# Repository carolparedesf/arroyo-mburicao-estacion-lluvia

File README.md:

# Sistema de adquisición y visualización de datos de sensores de lluvia
### Estaciones meteorológicas distribuidas — Arroyo Mburicao

---

## Descripción

Sistema de monitoreo pluviométrico distribuido a lo largo del arroyo Mburicao. Cada estación integra un sensor óptico de lluvia con comunicación RS485, una PCB propia basada en ESP32-S3 con componentes SMD, y transmisión de datos vía DTU con respaldo local en MicroSD. Los datos se visualizan en tiempo real a través de un dashboard web.

---

## Imágenes del hardware

| Render 3D | PCB | Placa soldada |
|---|---|---|
|  |  |  |

## Características principales

- Microcontrolador ESP32-S3 con componentes de montaje superficial (SMD)
- Sensor óptico de lluvia con interfaz RS485 / Modbus RTU
- Transmisión de datos vía DTU (RS485 canal 2)
- Almacenamiento local en MicroSD (`datalog.csv`) con cola de reintentos (`temp.csv`)
- RTC DS3231M para sincronización de slots de medición cada 60 segundos
- Alimentación con reductor a 3.3V
- Caja para intemperie compatible con la estructura de la estación meteorológica
- Dashboard web en tiempo real

---

## Estructura del repositorio

```
arroyo-mburicao-estacion-lluvia/
│
├── hardware/
│   └── Estacion_lluviaV4/
│       ├── BOM/                           # Lista de materiales
│       ├── images/                        # Renders 3D y fotos del PCB
│       ├── planos/                        # Planos técnicos 2D con cotas
│       ├── step/                          # Modelos 3D STEP
│       ├── Estacion_lluviaV4.kicad_pcb    # PCB
│       ├── Estacion_lluviaV4.kicad_sch    # Esquemático principal
│       ├── conector_USB.kicad_sch         # Sub-esquemático USB
│       ├── DS3231.kicad_sch               # Sub-esquemático RTC
│       ├── esp32_modulo.kicad_sch         # Sub-esquemático ESP32-S3
│       ├── sd_to_esp32.kicad_sch          # Sub-esquemático MicroSD
│       ├── ttl_to_rs485.kicad_sch         # Sub-esquemático RS485
│       └── vcc_to_3v3.kicad_sch           # Sub-esquemático alimentación
│
├── software/
│   ├── esp32s3_lluvia/                    # Proyecto principal ESP-IDF
│   │   ├── main/                          # Loop principal y pipeline
│   │   ├── components/                    # Drivers por módulo
│   │   │   ├── config/                    # Configuración de pines
│   │   │   ├── rtc/                       # Driver DS3231M (I2C)
│   │   │   ├── sdcard/                    # MicroSD (SPI + FAT)
│   │   │   ├── modbus_rtu/                # Modbus RTU (RS485 canal 1)
│   │   │   ├── dtu/                       # DTU (RS485 canal 2)
│   │   │   └── rs485/                     # Driver RS485 genérico
│   │   ├── CMakeLists.txt
│   │   └── sdkconfig                      # Configuración del proyecto
│   │
│   └── tests/                             # Pruebas aisladas por componente
│       ├── test_led/                      # Prueba LED debug
│       ├── test_rtc/                      # Prueba DS3231M
│       ├── test_sdcard/                   # Prueba MicroSD
│       └── test_modbus/                   # Prueba sensor lluvia Modbus RTU
│
├── mechanical/
│   ├── caja_tapa/                         # Modelo de la caja para intemperie
│   ├── ensamblaje/                        # Ensamblaje completo
│   └── soporte_sensor/                    # Estructura soporte del sensor
│
├── dashboard/
│   └── README.md                          # Link al repositorio del dashboard
│
└── docs/
    ├── report/                            # Informes de proceso y final
    └── photos/                            # Fotos del prototipo
```
---

## Hardware

### Diagrama de bloques

```
Sensor de lluvia (RS485/Modbus RTU)
            │
            ▼
        ESP32-S3
            ├── RTC DS3231M  (I2C)
            ├── MicroSD      (SPI)
            ├── RS485 canal 1 → Sensor de lluvia
            └── RS485 canal 2 → DTU → Base de datos en la nube
```

### Versiones del PCB

| Versión | Fecha | Estado |
|---|---|---|
| v1.0 | — | Fabricación inicial |
| v2.0 | — | Fabricación inicial |
| v3.0 | — | Fabricación inicial |
| v4.0 | — | En desarrollo |

Los archivos de fabricación se encuentran en `hardware/Estacion_lluviaV4/planos/`.

---

## Software

El código fuente del ESP32-S3 está desarrollado en **ESP-IDF (CMake)** e incluye drivers para RS485, Modbus RTU, DTU, RTC DS3231M y MicroSD.

| Módulo | Descripción |
|---|---|
| `esp32s3_lluvia` | Pipeline completo de medición y transmisión |
| `tests/test_led` | Prueba de LED de debug |
| `tests/test_rtc` | Prueba del RTC DS3231M |
| `tests/test_sdcard` | Prueba de MicroSD |
| `tests/test_modbus` | Prueba del sensor de lluvia vía Modbus RTU |

Ver descripción completa del flujo de operación en [`software/esp32s3_lluvia/README.md`](software/esp32s3_lluvia/README.md).

---

## Dashboard

El dashboard de visualización en línea está desarrollado en Next.js y desplegado en Vercel.

- 🔗 Repositorio: [hydromet-dashboard](https://github.com/carolparedesf/hydromet-dashboard)
- 🌐 Demo en vivo: [hydromet-dashboard.vercel.app](https://hydromet-dashboard.vercel.app)

---

## Costos

Ver lista de materiales completa en [`hardware/Estacion_lluviaV4/BOM/BOM_Estacion_lluviaV4.xlsx`](hardware/Estacion_lluviaV4/BOM/BOM_Estacion_lluviaV4.xlsx).

---

## Resultados

Las mediciones, pruebas y gráficas obtenidas se encuentran en [`docs/preiminary_results/`](docs/results_preiminary/).

---

## Equipo

| Integrante | Contacto |
|---|---|
| Victoria Paredes | carolparedesf@fiuna.edu.py |
| Francisco Gonzalez | frgonzalez@fiuna.edu.py  |
| Melissa Olmedo |  meliolmedo@fiuna.edu.py |

**Institución:** Universidad Nacional de Asunción — Facultad de Ingeniería
**Cátedra:** Proyecto 3 y 4

---

## Licencia

- Hardware: [CERN-OHL-P v2](LICENSE)
- Firmware: MIT
- Dashboard: MIT

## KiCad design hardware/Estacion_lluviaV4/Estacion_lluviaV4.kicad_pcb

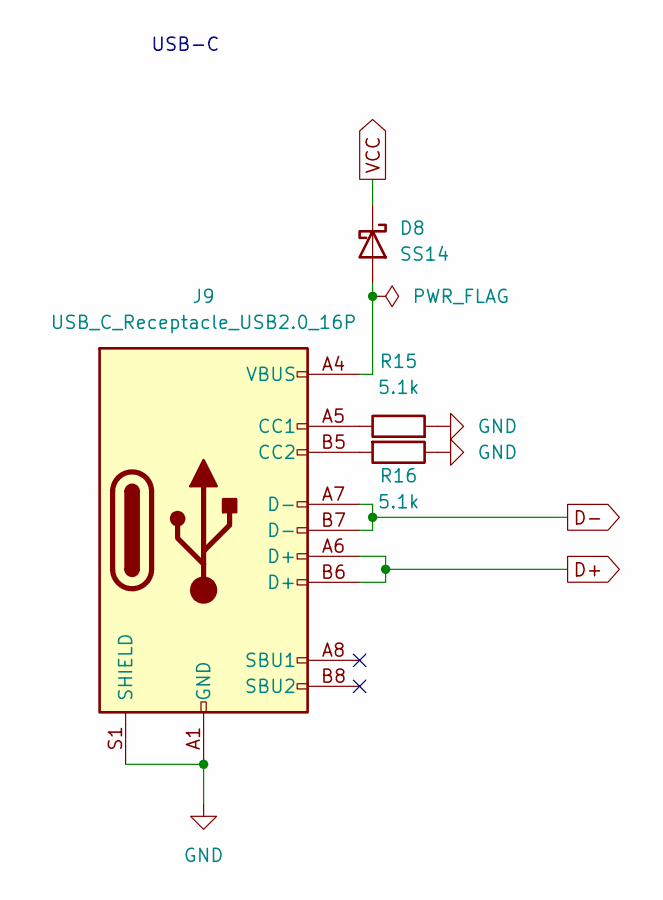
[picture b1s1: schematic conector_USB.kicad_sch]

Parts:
D8: SS14; D_SMA
J9: USB_C_Receptacle_USB2.0_16P; USB_C_Receptacle_Palconn_UTC16-G
R15, R16: 5.1k; R_0805_2012Metric_Pad1.20x1.40mm_HandSolder

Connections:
D+: J9.A6 (D+), J9.B6 (D+); also elsewhere on the board
D-: J9.A7 (D-), J9.B7 (D-); also elsewhere on the board
GND: J9.A1 (GND), J9.A12 (GND), J9.B1 (GND), J9.B12 (GND), J9.S1 (SHIELD), R15.2, R16.1; also elsewhere on the board
unnamed: D8.2 (A), J9.A4 (VBUS), J9.A9 (VBUS), J9.B4 (VBUS), J9.B9 (VBUS)
unnamed: J9.A5 (CC1), R15.1
unnamed: J9.B5 (CC2), R16.2
VCC: D8.1 (K); also elsewhere on the board

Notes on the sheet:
USB-C

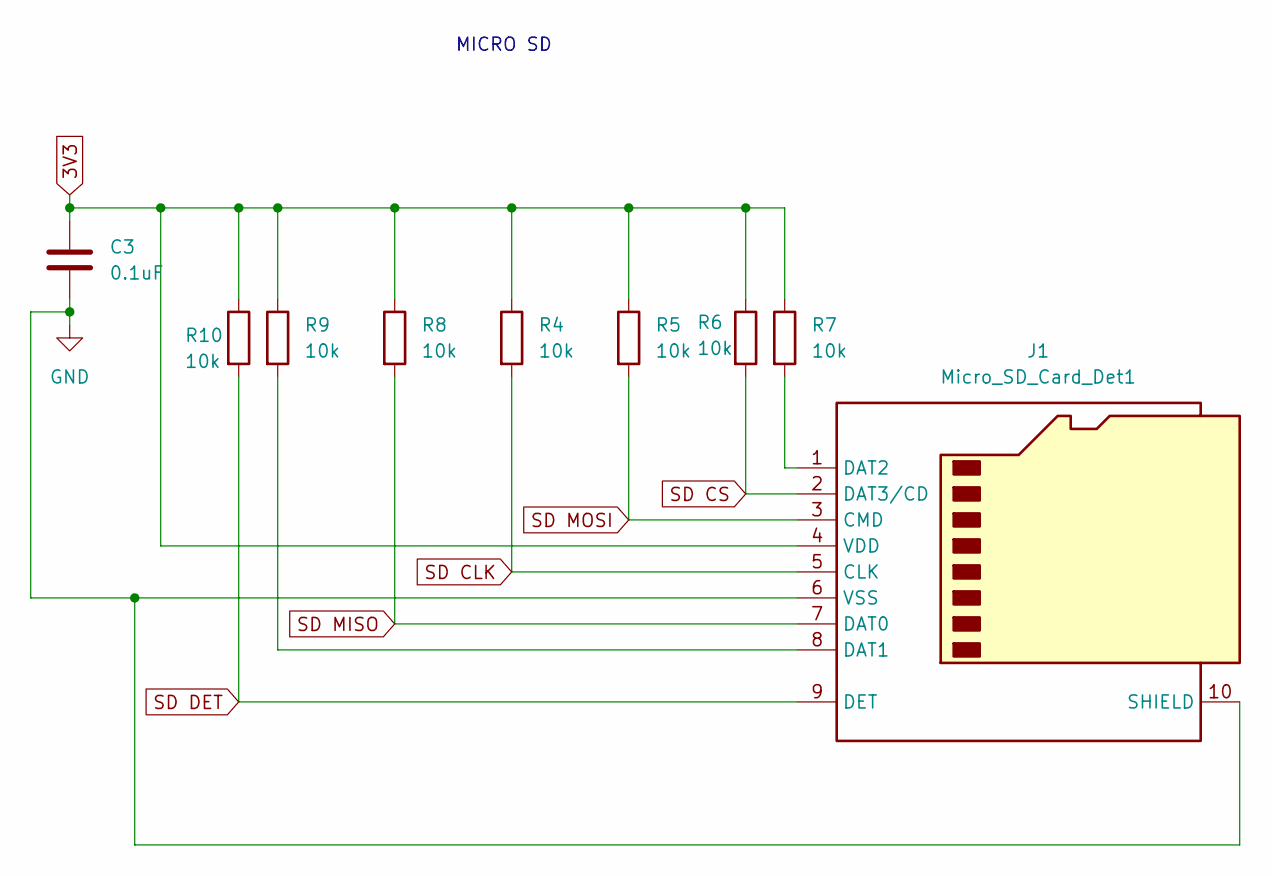
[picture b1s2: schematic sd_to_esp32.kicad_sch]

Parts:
C3: 0.1uF; C_0805_2012Metric_Pad1.18x1.45mm_HandSolder
J1: Micro_SD_Card_Det1; microSD_HC_Molex_104031-0811
R4, R5, R6, R7, R8, R9, R10: 10k; R_0805_2012Metric_Pad1.20x1.40mm_HandSolder

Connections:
3V3: C3.2, J1.4 (VDD), R4.1, R5.1, R6.1, R7.1, R8.1, R9.1, R10.1; also elsewhere on the board
GND: C3.1, J1.6 (VSS), J1.10 (SHIELD); also elsewhere on the board
unnamed: J1.8 (DAT1), R9.2
unnamed: J1.1 (DAT2), R7.2
SD CLK: J1.5 (CLK), R4.2; also elsewhere on the board
SD CS: J1.2 (DAT3/CD), R6.2; also elsewhere on the board
SD DET: J1.9 (DET), R10.2; also elsewhere on the board
SD MISO: J1.7 (DAT0), R8.2; also elsewhere on the board
SD MOSI: J1.3 (CMD), R5.2; also elsewhere on the board

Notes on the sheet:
MICRO SD

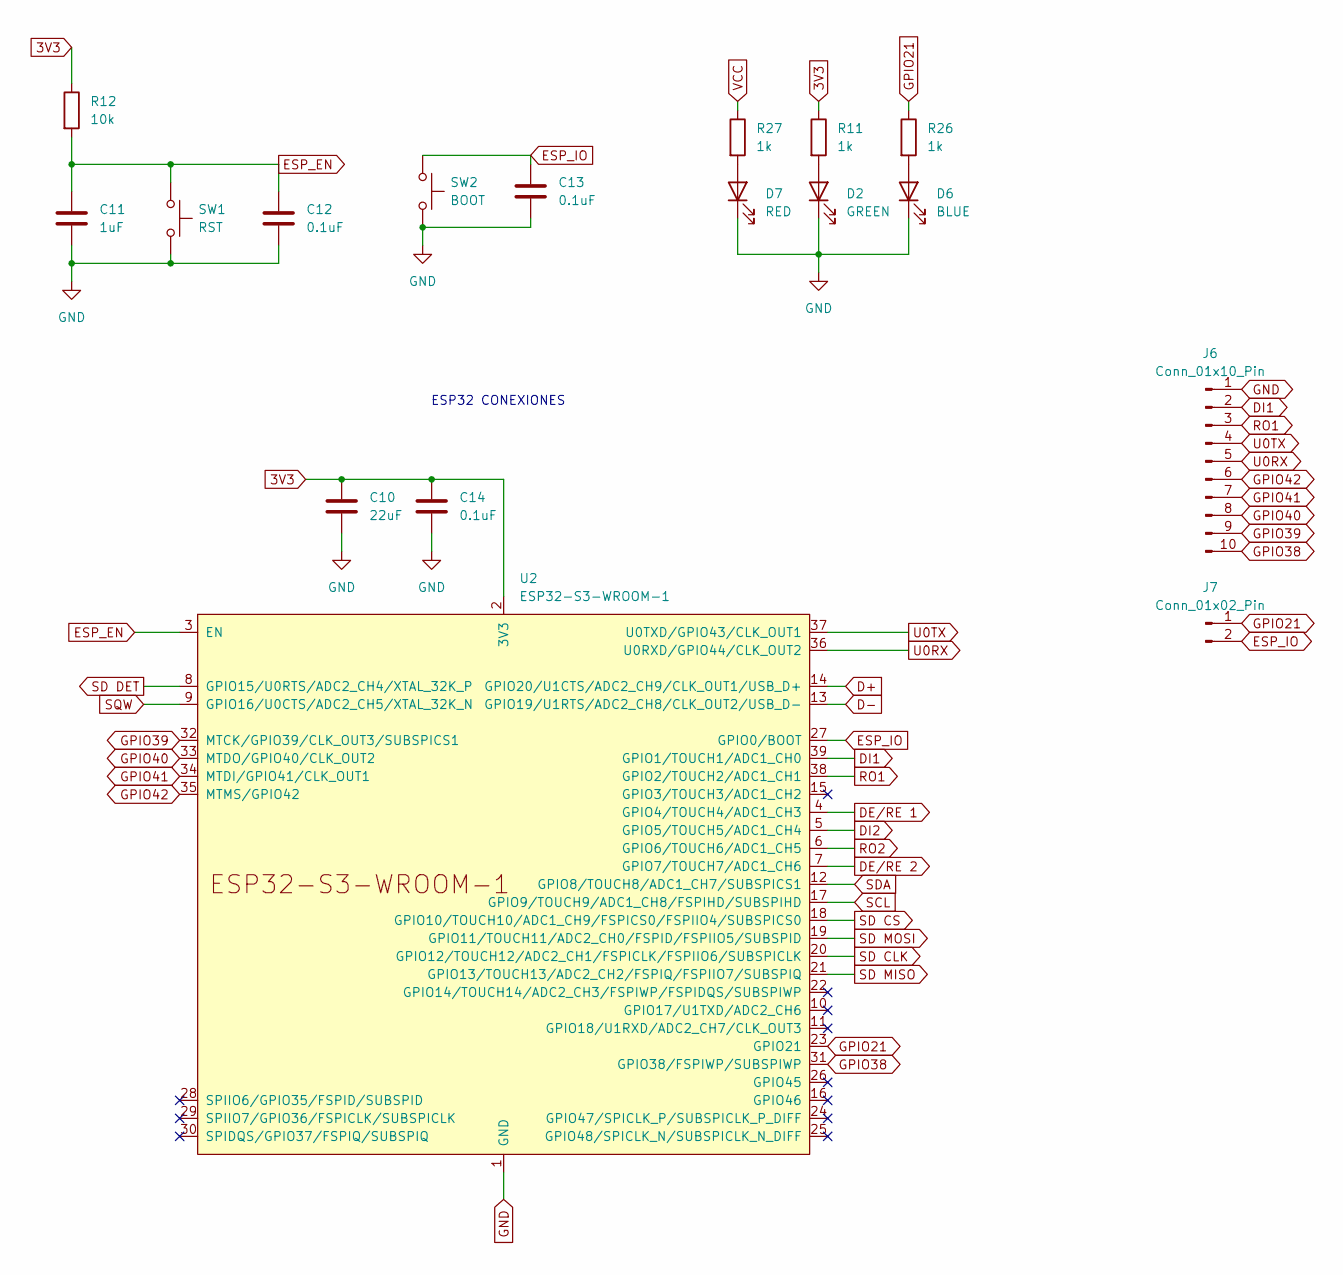
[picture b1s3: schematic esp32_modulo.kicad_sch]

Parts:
C10: 22uF; C_0805_2012Metric_Pad1.18x1.45mm_HandSolder
C11: 1uF; C_0805_2012Metric_Pad1.18x1.45mm_HandSolder
C12, C13, C14: 0.1uF; C_0805_2012Metric_Pad1.18x1.45mm_HandSolder
D2: GREEN; LED_0805_2012Metric_Pad1.15x1.40mm_HandSolder
D6: BLUE; LED_0805_2012Metric_Pad1.15x1.40mm_HandSolder
D7: RED; LED_0805_2012Metric_Pad1.15x1.40mm_HandSolder
J6: Conn_01x10_Pin; PinHeader_1x10_P2.54mm_Vertical
J7: Conn_01x02_Pin; PinHeader_1x02_P2.54mm_Vertical
R11, R26, R27: 1k; R_0805_2012Metric_Pad1.20x1.40mm_HandSolder
R12: 10k; R_0805_2012Metric_Pad1.20x1.40mm_HandSolder
SW1: RST; SW_Push_1P1T_NO_CK_KMR2
SW2: BOOT; SW_Push_1P1T_NO_CK_KMR2
U2: ESP32-S3-WROOM-1

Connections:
3V3: C10.2, C14.2, R11.1, R12.1, U2.2 (3V3); also elsewhere on the board
D+: U2.14 (GPIO20/U1CTS/ADC2_CH9/CLK_OUT1/USB_D+); also elsewhere on the board
D-: U2.13 (GPIO19/U1RTS/ADC2_CH8/CLK_OUT2/USB_D-); also elsewhere on the board
DE/RE 1: U2.4 (GPIO4/TOUCH4/ADC1_CH3); also elsewhere on the board
DE/RE 2: U2.7 (GPIO7/TOUCH7/ADC1_CH6); also elsewhere on the board
DI1: J6.2, U2.39 (GPIO1/TOUCH1/ADC1_CH0); also elsewhere on the board
DI2: U2.5 (GPIO5/TOUCH5/ADC1_CH4); also elsewhere on the board
ESP_EN: C11.2, C12.2, R12.2, SW1.1, U2.3 (EN)
ESP_IO: C13.2, J7.2, SW2.1, U2.27 (GPIO0/BOOT)
GND: C10.1, C11.1, C12.1, C13.1, C14.1, D2.1 (K), D6.1 (K), D7.1 (K), J6.1, SW1.2, SW2.2, U2.1 (GND), U2.40 (GND), U2.41 (GND); also elsewhere on the board
GPIO21: J7.1, R26.1, U2.23 (GPIO21)
GPIO38: J6.10, U2.31 (GPIO38/FSPIWP/SUBSPIWP)
GPIO39: J6.9, U2.32 (MTCK/GPIO39/CLK_OUT3/SUBSPICS1)
GPIO40: J6.8, U2.33 (MTDO/GPIO40/CLK_OUT2)
GPIO41: J6.7, U2.34 (MTDI/GPIO41/CLK_OUT1)
GPIO42: J6.6, U2.35 (MTMS/GPIO42)
unnamed: D2.2 (A), R11.2
unnamed: D6.2 (A), R26.2
unnamed: D7.2 (A), R27.2
RO1: J6.3, U2.38 (GPIO2/TOUCH2/ADC1_CH1); also elsewhere on the board
RO2: U2.6 (GPIO6/TOUCH6/ADC1_CH5); also elsewhere on the board
SCL: U2.17 (GPIO9/TOUCH9/ADC1_CH8/FSPIHD/SUBSPIHD); also elsewhere on the board
SD CLK: U2.20 (GPIO12/TOUCH12/ADC2_CH1/FSPICLK/FSPIIO6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); also elsewhere on the board
SD CS: U2.18 (GPIO10/TOUCH10/ADC1_CH9/FSPICS0/FSPIIO4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); also elsewhere on the board
SD DET: U2.8 (GPIO15/U0RTS/ADC2_CH4/XTAL_32K_P); also elsewhere on the board
SD MISO: U2.21 (GPIO13/TOUCH13/ADC2_CH2/FSPIQ/FSPIIO7/S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); also elsewhere on the board
SD MOSI: U2.19 (GPIO11/TOUCH11/ADC2_CH0/FSPID/FSPIIO5/S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); also elsewhere on the board
SDA: U2.12 (GPIO8/TOUCH8/ADC1_CH7/SUBSPICS1); also elsewhere on the board
SQW: U2.9 (GPIO16/U0CTS/ADC2_CH5/XTAL_32K_N); also elsewhere on the board
U0RX: J6.5, U2.36 (U0RXD/GPIO44/CLK_OUT2)
U0TX: J6.4, U2.37 (U0TXD/GPIO43/CLK_OUT1)
VCC: R27.1; also elsewhere on the board

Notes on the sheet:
ESP32 CONEXIONES

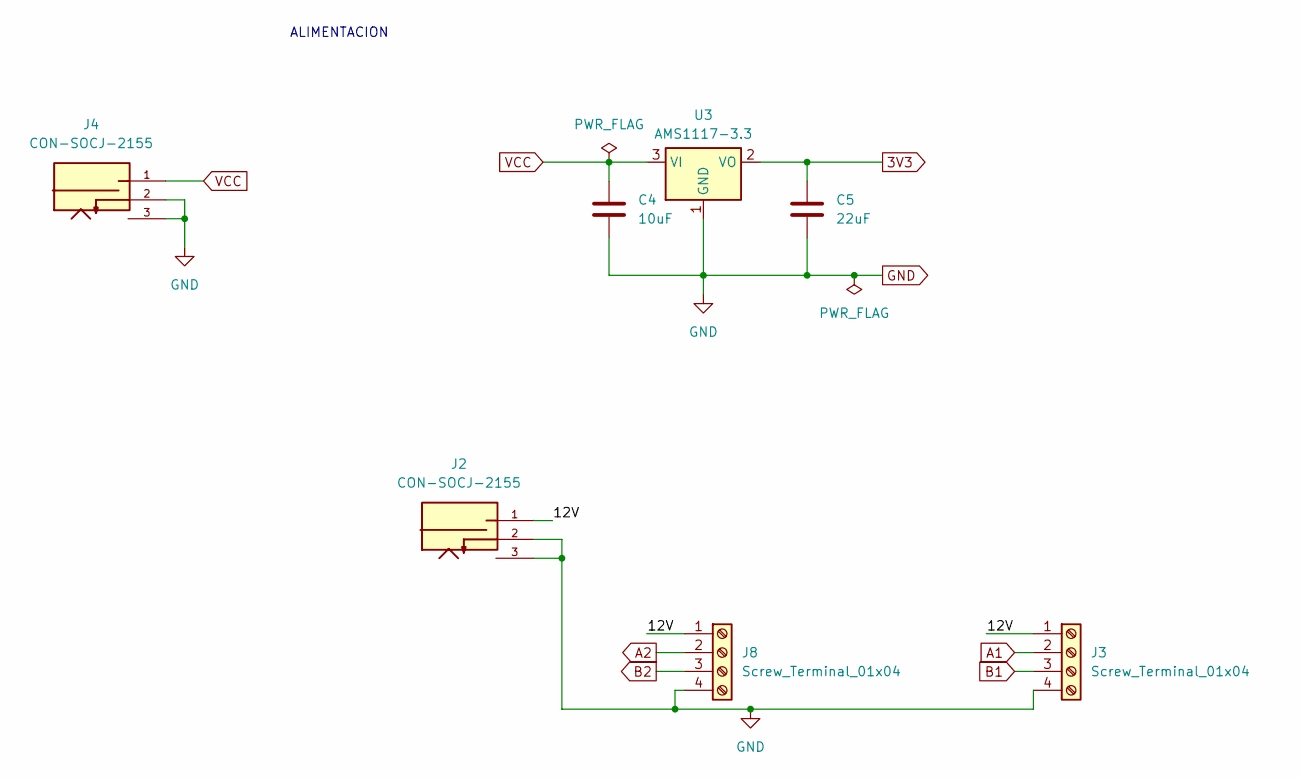
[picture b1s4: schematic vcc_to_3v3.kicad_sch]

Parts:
C4: 10uF; C_0805_2012Metric_Pad1.18x1.45mm_HandSolder
C5: 22uF; C_0805_2012Metric_Pad1.18x1.45mm_HandSolder
J2, J4: CON-SOCJ-2155; PARTREV NA
J3, J8: Screw_Terminal_01x04; TerminalBlock_MaiXu_MX126-5.0-04P_1x04_P5.00mm
U3: AMS1117-3.3; SOT-223-3_TabPin2

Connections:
3V3: C5.2, U3.2 (VO); also elsewhere on the board
/alimentacion/12V: J2.1, J3.1, J8.1
A1: J3.2; also elsewhere on the board
A2: J8.2; also elsewhere on the board
B1: J3.3; also elsewhere on the board
B2: J8.3; also elsewhere on the board
GND: C4.1, C5.1, J2.2, J2.3, J3.4, J4.2, J4.3, J8.4, U3.1 (GND); also elsewhere on the board
VCC: C4.2, J4.1, U3.3 (VI); also elsewhere on the board

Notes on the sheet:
ALIMENTACION

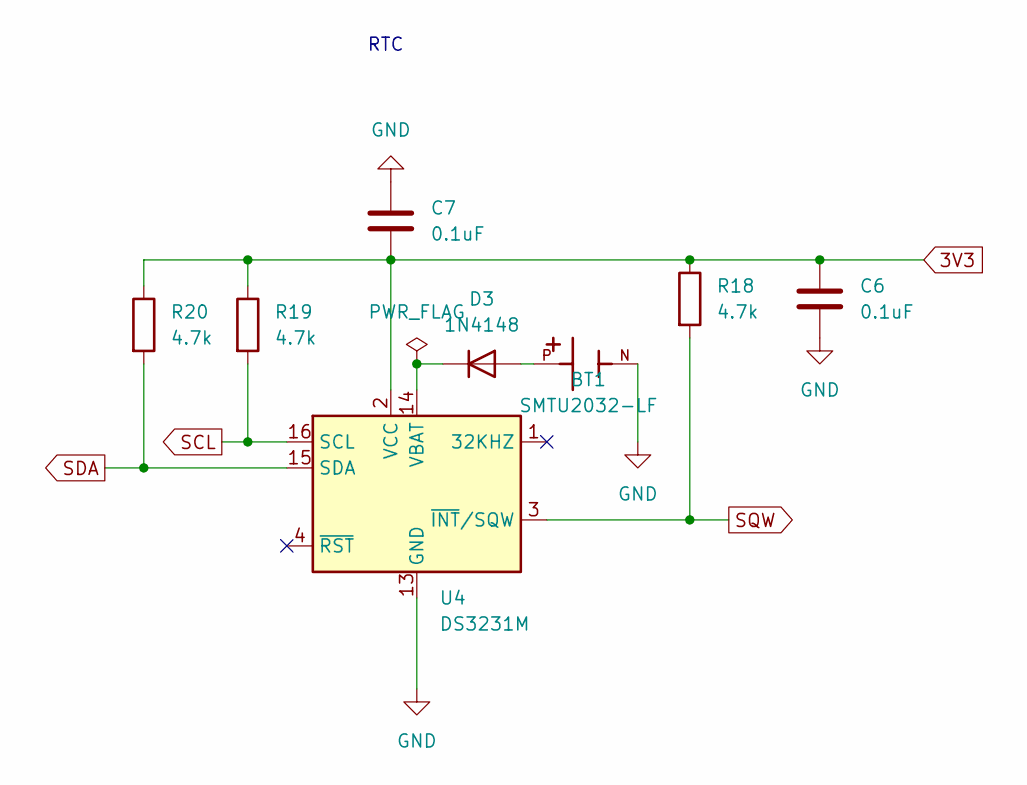
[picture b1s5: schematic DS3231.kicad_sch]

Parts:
BT1: SMTU2032-LF; BAT_SMTU2032-LF; PARTREV 3
C6, C7: 0.1uF; C_0805_2012Metric_Pad1.18x1.45mm_HandSolder
D3: 1N4148; D_SOD-123
R18, R19, R20: 4.7k; R_0805_2012Metric_Pad1.20x1.40mm_HandSolder
U4: DS3231M; SOIC-16W_7.5x10.3mm_P1.27mm

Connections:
3V3: C6.2, C7.1, R18.1, R19.1, R20.1, U4.2 (VCC); also elsewhere on the board
GND: BT1.N, C6.1, C7.2, U4.5 (GND), U4.6 (GND), U4.7 (GND), U4.8 (GND), U4.9 (GND), U4.10 (GND), U4.11 (GND), U4.12 (GND), U4.13 (GND); also elsewhere on the board
unnamed: BT1.P, D3.2 (A)
unnamed: D3.1 (K), U4.14 (VBAT)
SCL: R19.2, U4.16 (SCL); also elsewhere on the board
SDA: R20.2, U4.15 (SDA); also elsewhere on the board
SQW: R18.2, U4.3 (~INT/SQW); also elsewhere on the board

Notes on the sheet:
RTC

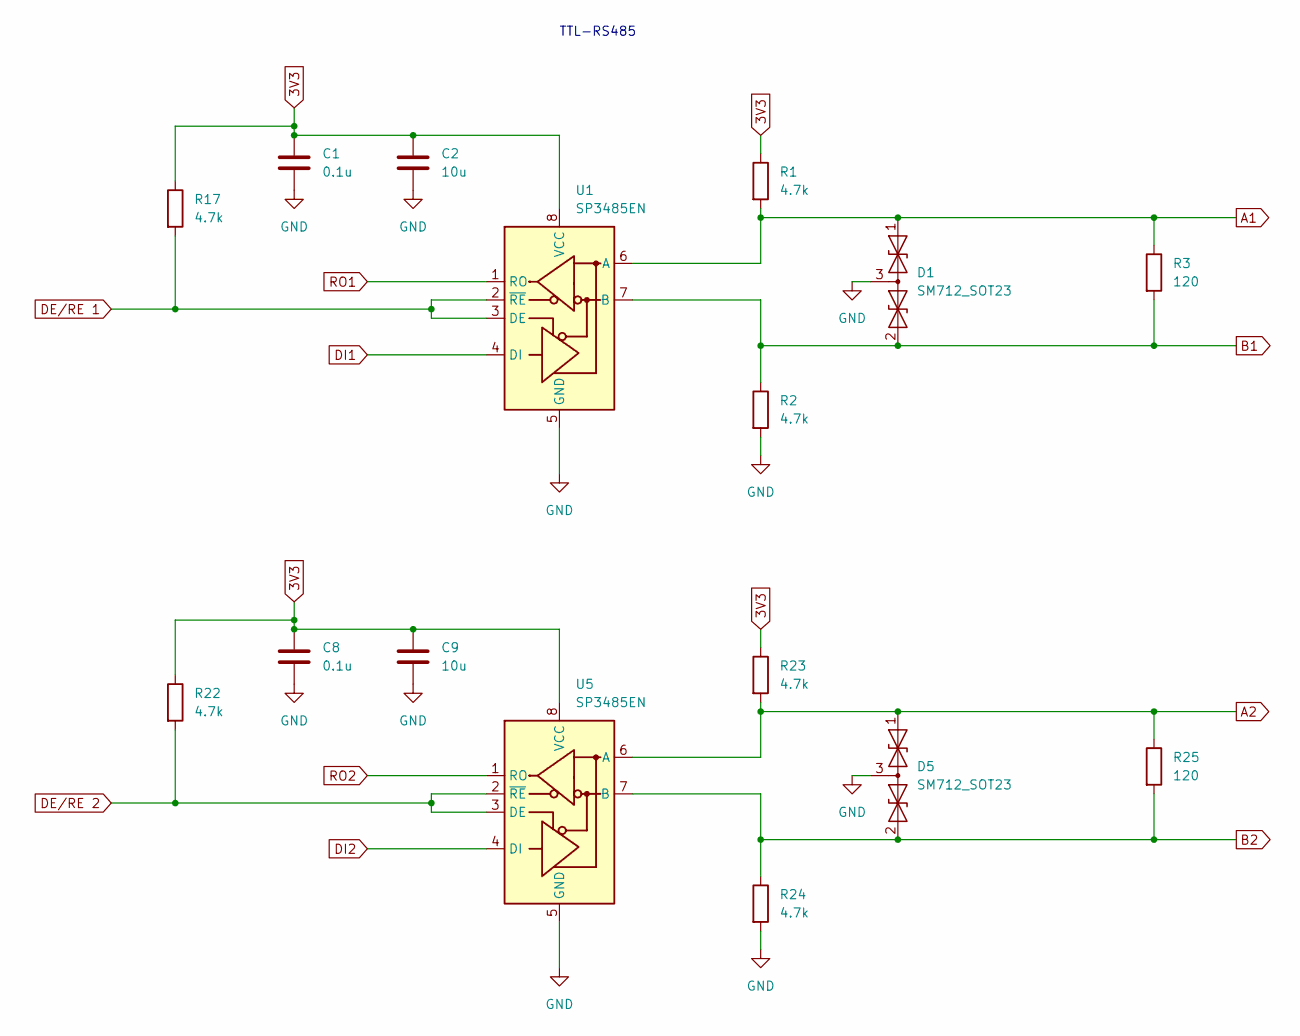
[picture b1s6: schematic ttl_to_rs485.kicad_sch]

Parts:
C1, C8: 0.1u; C_0805_2012Metric_Pad1.18x1.45mm_HandSolder
C2, C9: 10u; C_0805_2012Metric_Pad1.18x1.45mm_HandSolder
D1, D5: SM712_SOT23; SOT-23
R1, R2, R17, R22, R23, R24: 4.7k; R_0805_2012Metric_Pad1.20x1.40mm_HandSolder
R3, R25: 120; R_0805_2012Metric_Pad1.20x1.40mm_HandSolder
U1, U5: SP3485EN; SOIC-8_3.9x4.9mm_P1.27mm

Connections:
3V3: C1.1, C2.1, C8.1, C9.1, R1.1, R17.1, R22.1, R23.1, U1.8 (VCC), U5.8 (VCC); also elsewhere on the board
A1: D1.1 (A1), R1.2, R3.1, U1.6 (A); also elsewhere on the board
A2: D5.1 (A1), R23.2, R25.1, U5.6 (A); also elsewhere on the board
B1: D1.2 (A2), R2.1, R3.2, U1.7 (B); also elsewhere on the board
B2: D5.2 (A2), R24.1, R25.2, U5.7 (B); also elsewhere on the board
DE/RE 1: R17.2, U1.2 (~RE), U1.3 (DE); also elsewhere on the board
DE/RE 2: R22.2, U5.2 (~RE), U5.3 (DE); also elsewhere on the board
DI1: U1.4 (DI); also elsewhere on the board
DI2: U5.4 (DI); also elsewhere on the board
GND: C1.2, C2.2, C8.2, C9.2, D1.3 (common), D5.3 (common), R2.2, R24.2, U1.5 (GND), U5.5 (GND); also elsewhere on the board
RO1: U1.1 (RO); also elsewhere on the board
RO2: U5.1 (RO); also elsewhere on the board

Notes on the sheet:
TTL-RS485

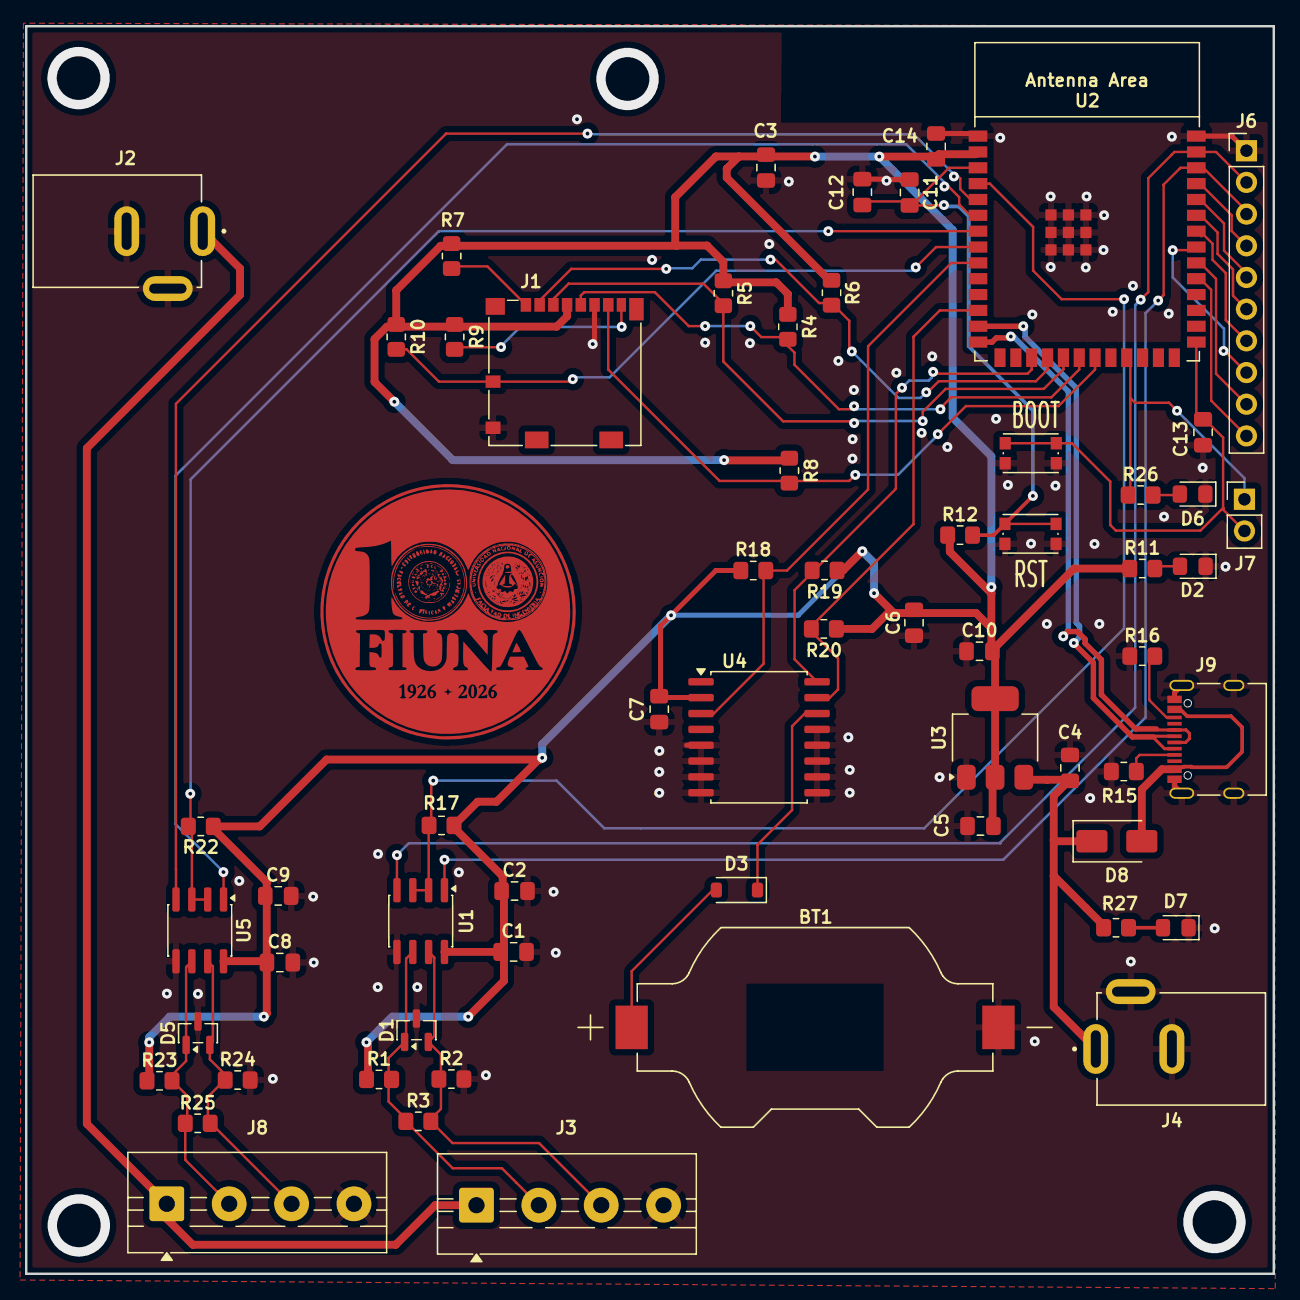
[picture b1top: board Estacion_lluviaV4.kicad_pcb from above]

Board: 2 copper layers, 100.0 x 100.0 mm, 61 parts (0 on the bottom side), 44 nets.

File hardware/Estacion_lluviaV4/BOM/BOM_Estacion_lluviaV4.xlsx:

Id | Identificador | Identificación | Huella | Cantidad | URL pedido | Mfr. No | Obs
1 | D6 | BLUE | LED_0805_2012Metric_Pad1.15x1.40mm_HandSolder | 1 | https://mou.sr/4caFJC0 | LSM0805463V
2 | R4,R9,R12,R5,R8,R7,R10,R6 | 10k | R_0805_2012Metric_Pad1.20x1.40mm_HandSolder | 8 | https://mou.sr/4bZL6VQ | RE0805FRE1010KL
3 | R23,R19,R17,R22,R20,R18,R24,R1,R2 | 4.7k | R_0805_2012Metric_Pad1.20x1.40mm_HandSolder | 9 | https://mou.sr/3O9f3K0 | AT0805FRE074K7L
4 | C14,C7,C13,C3,C6,C12,C1,C8 | 0.1uF | C_0805_2012Metric_Pad1.18x1.45mm_HandSolder | 8 | https://mou.sr/3O7dfRJ | AS0805KKX7R9BB104
5 | R3,R25 | 0.12k | R_0805_2012Metric_Pad1.20x1.40mm_HandSolder | 2 | https://mou.sr/4vq4YJq | AF0805FR-07120RL | solo r3
6 | U2 | ESP32-S3-WROOM-1 | ESP32-S3-WROOM-1 | 1 | https://mou.sr/4vmADew | ESP32-S3-WROOM-1-N8R8
7 | C5,C10 | 22uF | C_0805_2012Metric_Pad1.18x1.45mm_HandSolder | 2 | https://mou.sr/4t9MpaY | CC0805MKX5R7BB226
8 | J3,J4,J5 | Screw_Terminal_01x02 | TerminalBlock_MaiXu_MX126-5.0-02P_1x02_P5.00mm | 3 | https://mou.sr/4vie9vi | 282856-2
9 | D7 | RED | LED_0805_2012Metric_Pad1.15x1.40mm_HandSolder | 1 | https://mou.sr/4cyCo0N | LSM0805412V
10 | U1,U5 | SP3485EN | SOIC-8_3.9x4.9mm_P1.27mm | 2 | https://mou.sr/4dETco8 | SP3485EN-L/TR
11 | D1,D5 | SM712_SOT23 | SOT-23 | 2 | https://mou.sr/3Q1NYsH | SM712-TP
12 | J7 | Conn_01x02_Pin | PinHeader_1x02_P1.00mm_Vertical | 1 | local | - | proveedor local
13 | D2 | GREEN | LED_0805_2012Metric_Pad1.15x1.40mm_HandSolder | 1 | https://mou.sr/4sqT539 | LSM0805452V
14 | SW1 | RST | SW_Push_1P1T_NO_CK_KMR2 | 1 | https://mou.sr/4srFPeF | KMR223G LFG
15 | J8 | Screw_Terminal_01x04 | TerminalBlock_MaiXu_MX126-5.0-04P_1x04_P5.00mm | 1 | https://mou.sr/3OypUx7 | 282856-4
16 | SW2 | BOOT | SW_Push_1P1T_NO_CK_KMR2 | 1 | https://mou.sr/4srFPeF | KMR223G LFG
17 | J9 | USB_C_Receptacle_USB2.0_16P | USB_C_Receptacle_Palconn_UTC16-G | 1 | https://mou.sr/4vrddFc | USB4930-00-A
18 | D8 | SS14 | D_SMA | 1 | https://mou.sr/4eaQiHI | VS-MBRA140TRPBF
19 | J1 | Micro_SD_Card_Det1 | microSD_HC_Molex_104031-0811 | 1 | https://mou.sr/41WAL70 | 104031-0811
20 | R15,R16 | 5.1k | R_0805_2012Metric_Pad1.20x1.40mm_HandSolder | 2 | https://mou.sr/47RTEvu | RC0805JR-105K1L
21 | C4,C9,C2 | 10uF | C_0805_2012Metric_Pad1.18x1.45mm_HandSolder | 3 | https://mou.sr/4tH0cWg | C0805X106K9RACTU
22 | C11 | 1uF | C_0805_2012Metric_Pad1.18x1.45mm_HandSolder | 1 | https://mou.sr/4t2ahx1 | C0805C105J4RAC7210
23 | R27,R26,R11 | 1k | R_0805_2012Metric_Pad1.20x1.40mm_HandSolder | 3 | https://mou.sr/3O9mlgQ | AC0805FR-131KL
24 | BT1 | SMTU2032-LF | BAT_SMTU2032-LF | 1 | https://mou.sr/4cb3Rpv | SMTU2032-C.TR
25 | D3 | 1N4148 | D_SOD-123 | 1 | https://mou.sr/4dESVBC | 1N4148W-HG3-08
26 | J6 | Conn_01x10_Pin | PinHeader_1x10_P1.00mm_Vertical | 1 | local | - | proveedor local
27 | U4 | DS3231M | SOIC-16W_7.5x10.3mm_P1.27mm | 1 | https://mou.sr/4mnJYPk | DS3231M+TRL
28 | U3 | AMS1117-3.3 | SOT-223-3_TabPin2 | 1 | https://mou.sr/41t8jcS | LDL1117S33R

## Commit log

2026-03-24 Voy a subir los archivos
2026-03-24 Se agregaron nuevos archivos
2026-06-01 station code + tests /
2026-06-01 mechanis changes
2026-06-01 changes on operation flow
2026-06-01 Initial commit - hardware, software, mechanical and docs structure
2026-06-01 fix: placa soldada
2026-06-01 Add soldered board photo
2026-06-01 fix photos
